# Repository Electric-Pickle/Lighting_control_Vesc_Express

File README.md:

Lighting control Board For Vesc Based Pev's

THIS Branch Will be updated once there is a working tested design 

Features
* onboard 5v2a buck 160v in (turned on and off via CAN or SERIAL ports)
* 3 level shifted LED ws2812 or similar outputs, + 2 onboard 
* onboard USB-C (diode added for brains to be powered VIA usb)
* onboard CAN termination (solder jumper to activate)
* duck

Ordering,
* Gerbers are prepped for PCB fab and assembly service,
* board must be 0.6mm thick (has to be advanced anyways for the C3 mini) ¯\_(ツ)_/¯
* I've preordered the buck, but JLC doesnt stock it, easy enough to solder by hand(caution board is very dense)

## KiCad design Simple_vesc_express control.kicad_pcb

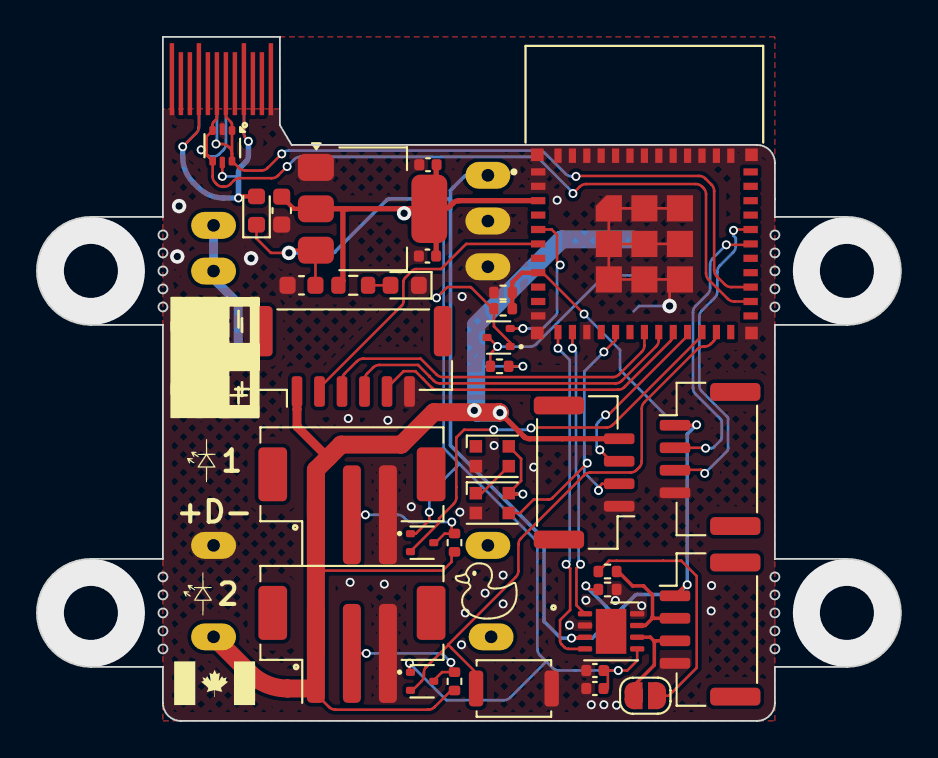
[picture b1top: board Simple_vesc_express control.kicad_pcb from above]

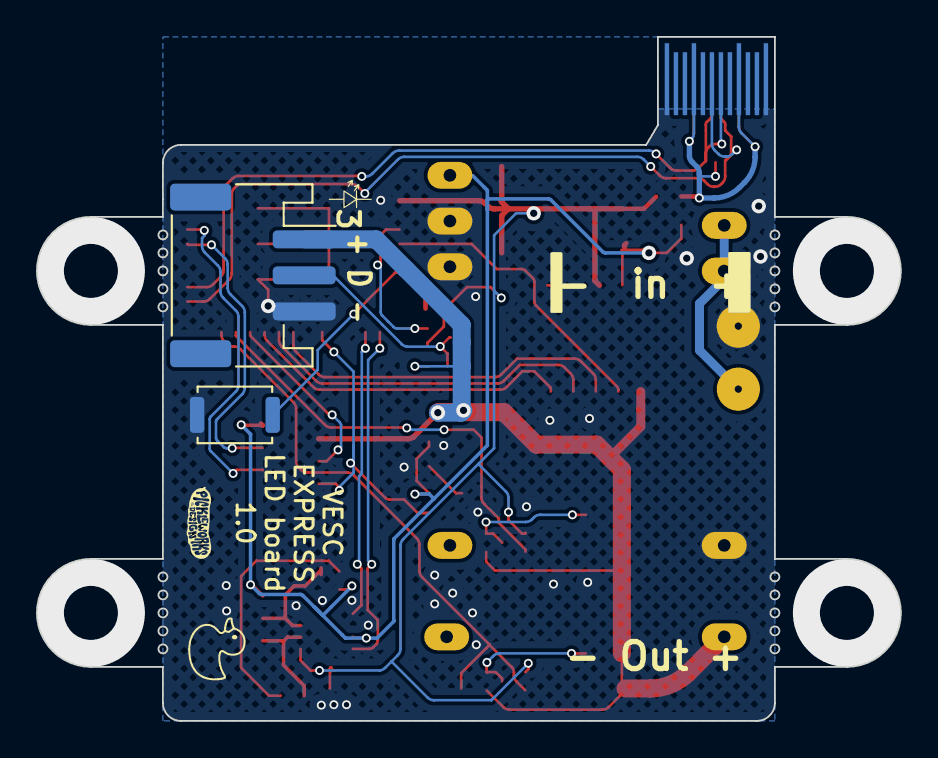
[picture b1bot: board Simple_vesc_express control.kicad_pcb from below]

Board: 2 copper layers, 48.0 x 38.0 mm, 38 parts (3 on the bottom side), 30 nets.

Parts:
C1: 1uf; R_0402_1005Metric
C3, C10: 10uF; C_0402_1005Metric
C4, C11: 100n; C_0402_1005Metric
C8, C9: 1uF; C_0603_1608Metric
D1: D_Small; D_0603_1608Metric
D2: red; LED_0603_1608Metric
D3, D4: WS2812B-2020; LED_WS2812B-2020_PLCC4_2.0x2.0mm
J1, J2, J9: Conn_01x04; JST_GH_BM04B-GHS-TBT_1x04-1MP_P1.25mm_Vertical
J4: USB_C_Receptacle_USB2.0; Cursed_usbc
J5, J6: Conn_01x03; JST_PH_B3B-PH-SM4-TB_1x03-1MP_P2.00mm_Vertical
J7: Conn_01x03; JST_PH_S3B-PH-SM4-TB_1x03-1MP_P2.00mm_Horizontal
J8: Conn_01x02; solder_power
J10: Conn_01x06; JST_GH_BM06B-GHS-TBT_1x06-1MP_P1.25mm_Vertical
JP1: Jumper_2_Open; SolderJumper-2_P1.3mm_Open_RoundedPad1.0x1.5mm
Q1, Q2, Q3: NMOS; SOT-523
R1: 120r; R_0402_1005Metric
R2, R3, R4: 3k3; R_0402_1005Metric
R5: 1k; R_0603_1608Metric
R6, R7: 10k; R_0402_1005Metric
SW1, SW2: SW_Push; SW_Push_SPST_NO_Alps_SKRK
U1: ESP32-C3-MINI-1-N4
U2: TCAN1042DRQ1; ATA6561-GBQW-N
U3: DCDC; RSDW10-05H
U5: AMS1117-3.3; SOT-223-3_TabPin2
U6: USBLC6-2P6; SOT-666

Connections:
!rst: C1.1, R6.1, SW2.1, U1.8 (EN)
+3V3: C3.1, C4.1, C9.1, C10.1, C11.1, Q1.1 (G), Q2.1 (G), Q3.1 (G), R5.1, R6.2, U1.3 (3V3), U2.5 (VIO), U5.2 (VO)
+5V: J5.1, J6.1, J7.1, J9.4, J10.1, R2.1, R3.1, R4.1, U3.14 (+VOUT)
+BATT: J8.1, U3.22 (+VIN), U3.23 (+VIN)
CAN+: J2.2, R1.1, U2.7 (CANH)
CAN-: J2.3, JP1.1 (A), U2.6 (CANL)
CAN_RX: U1.12 (IO0), U2.4 (RXD)
CAN_TX: U1.13 (IO1), U2.1 (TXD)
D+: J4.A6 (D+), J4.B6 (D+), U1.27 (IO19), U6.1 (I/O1), U6.6 (I/O1)
D-: J4.A7 (D-), J4.B7 (D-), U1.26 (IO18), U6.3 (I/O2), U6.4 (I/O2)
GND: C1.2, C3.2, C4.2, C8.2, C9.2, C10.2, C11.2, D2.1 (K), D3.2 (VSS), D4.2 (VSS), J1.4, J2.4, J4.A1 (GND), J4.A12 (GND), J4.B1 (GND), J4.B12 (GND), J5.3, J6.3, J7.3, J8.2, J9.1, J10.6, R7.2, SW1.2, SW2.2, U1.1 (GND), U1.2 (GND), U1.11 (GND), U1.14 (GND), U1.36 (GND), U1.37 (GND), U1.38 (GND), U1.39 (GND), U1.40 (GND), U1.41 (GND), U1.42 (GND), U1.43 (GND), U1.44 (GND), U1.45 (GND), U1.46 (GND), U1.47 (GND), U1.48 (GND), U1.49_1 (GND), U1.49_2 (GND), U1.49_3 (GND), U1.49_4 (GND), U1.49_5 (GND), U1.49_6 (GND), U1.49_7 (GND), U1.49_8 (GND), U1.49_9 (GND), U1.50 (GND), U1.51 (GND), U1.52 (GND), U1.53 (GND), U2.2 (GND), U2.8 (STB), U3.2 (-VIN), U3.3 (-VIN), U3.16 (-VOUT), U5.1 (GND), U6.2 (GND)
IO-3: J10.2, U1.6 (IO3)
IO-4: J10.3, U1.18 (IO4)
IO-5: J10.4, U1.19 (IO5)
IO-6: J10.5, U1.20 (IO6)
IO-7: J9.3, U1.21 (IO7)
IO-10: D4.3 (DIN), J9.2, U1.16 (IO10)
unnamed: D1.2 (A), J4.A4 (VBUS), J4.A9 (VBUS), J4.B4 (VBUS), J4.B9 (VBUS), U6.5 (VBUS)
unnamed: D2.2 (A), R5.2
unnamed: D3.3 (DIN), D4.1 (DOUT)
unnamed: JP1.2 (B), R1.2
RX: J1.2, U1.30 (RXD0)
TX: J1.3, U1.31 (TXD0)
en: C8.1, D1.1 (K), D3.4 (VDD), D4.4 (VDD), J1.1, J2.1, R7.1, U2.3 (VCC), U3.1 (ON/~OFF), U5.3 (VI)
led1 3v: Q1.2 (S), U1.22 (IO8)
led1 5v: J5.2, Q1.3 (D), R2.2
led2 3v: Q2.2 (S), SW1.1, U1.23 (IO9)
led2 5v: J6.2, Q2.3 (D), R3.2
led3 3v: Q3.2 (S), U1.5 (IO2)
led3 5v: J7.2, Q3.3 (D), R4.2

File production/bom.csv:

Designator,Footprint,Quantity,Value,LCSC Part #
C1,0402,1,1uf,C52923
"C10, C3",0402,2,10uF,C15525
"C11, C4",0402,2,100n,C1525
"C8, C9",0603,2,1uF,C15849
D1,0603,1,D_Small,C143772
D2,0603,1,red,C72044
"D3, D4",LED_WS2812B-2020_PLCC4_2.0x2.0mm,2,WS2812B-2020,C965555
"J1, J2, J9",JST_GH_BM04B-GHS-TBT_1x04-1MP_P1.25mm_Vertical,3,Conn_01x04,C161692
J10,JST_GH_BM06B-GHS-TBT_1x06-1MP_P1.25mm_Vertical,1,Conn_01x06,     C189892
"J5, J6",JST_PH_B3B-PH-SM4-TB_1x03-1MP_P2.00mm_Vertical,2,Conn_01x03,C160353
J7,JST_PH_S3B-PH-SM4-TB_1x03-1MP_P2.00mm_Horizontal,1,Conn_01x03,C265101
"Q1, Q2, Q3",SOT-523,3,NMOS, C5224244 
R1,0402,1,120r,C25079
"R2, R3, R4",0402,3,3k3,C25890 
R5,0603,1,1k,C21190
"R6, R7",0402,2,10k,C25744
"SW1, SW2",SW_Push_SPST_NO_Alps_SKRK,2,SW_Push,C720477
U1,ESP32-C3-MINI-1-N4,1,ESP32-C3-MINI-1-N4,C2934569
U2,ATA6561-GBQW-N,1,TCAN1042DRQ1,C5308062
U3,RSDW10-05H,1,DCDC,C5872541
U5,SOT-223-3_TabPin2,1,AMS1117-3.3,C6186
U6,SOT-666,1,USBLC6-2P6,C2827693

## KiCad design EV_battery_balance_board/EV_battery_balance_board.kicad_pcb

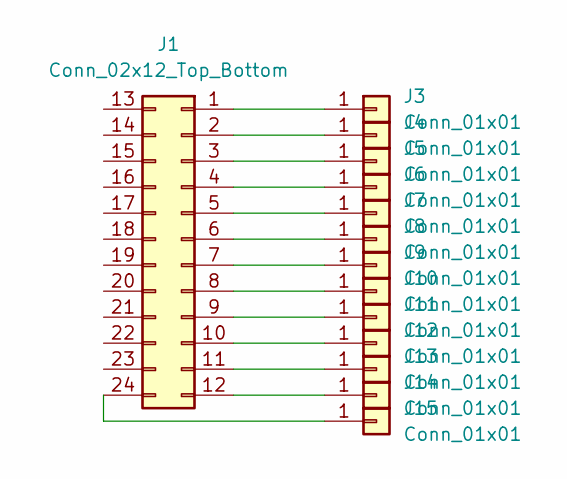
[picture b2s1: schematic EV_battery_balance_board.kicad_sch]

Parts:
J1: Conn_02x12_Top_Bottom; 1318853-2
J3, J4, J5, J6, J7, J8, J9, J10, J11, J12, J13, J14, J15: Conn_01x01; Wuerth_REDCUBE-THR_WP-THRBU_74650073_THR

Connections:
unnamed: J1.1, J3.1
unnamed: J1.2, J4.1
unnamed: J1.3, J5.1
unnamed: J1.4, J6.1
unnamed: J1.5, J7.1
unnamed: J1.6, J8.1
unnamed: J1.7, J9.1
unnamed: J1.8, J10.1
unnamed: J1.9, J11.1
unnamed: J1.10, J12.1
unnamed: J1.11, J13.1
unnamed: J1.12, J14.1
unnamed: J1.24, J15.1

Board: 2 copper layers, 14 parts (1 on the bottom side), 13 nets, no tracks yet.

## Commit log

2024-07-31 first initial Commit
2024-07-31 changed usb powered parts
2024-07-31 caution
2024-07-31 no tested designs yet
2024-08-01 removed files, tracking
